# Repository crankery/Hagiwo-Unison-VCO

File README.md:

# Hagiwo Unison VCO

> [!NOTE]
> This is a work in progress, I'm sure I made a mistake somewhere I'll post an update when I receive the first batch of boards. 

If you don't know Hagiwo, check out their [YouTube channel](https://www.youtube.com/@HAGIWO). He puts out new DIY Eurorack module designs all the time.

This is (what is currently) has latest module, the [Unison VCO](https://note.com/solder_state/n/na0ae5754fa9c). All I've done is switch to SMT devices to try to fit it all on a single 6hp PCB. All credit for the circuit design go to Hagiwo.

The PCB is 100x30mm so it should be pretty darned cheap to order from one of the fabs over in China. Higawo used a [Seeed Studio XIAO RA4M1](https://wiki.seeedstudio.com/getting_started_xiao_ra4m1/) microcontroller module on this one, which are about $5 ordered from Seeed. They're really quite neat.

I added a tiny OLED display module to show the currently selected waveform. The display module is available from all the usual places with with search terms like "0.42" 0.42 Inch White OLED Display LCD Module 72X40 Serial Screen White Color I2C IIC/SPI Interface SSD1306". I'm sure there's an original manufacturer of these things but I can't figure it out. The 4 pin I2C SSD1306 version that looks like this:

TODO: make incredibly insightful comments about stuff here

## Main Board

Here's some renderings of this thing. I'll take pictures of it when I actually build it.

## Front Panel

I created a Eurorack 6hp front panel for this in KiCad. Which is weird but hey. I don't want to pay for aluminum panels.

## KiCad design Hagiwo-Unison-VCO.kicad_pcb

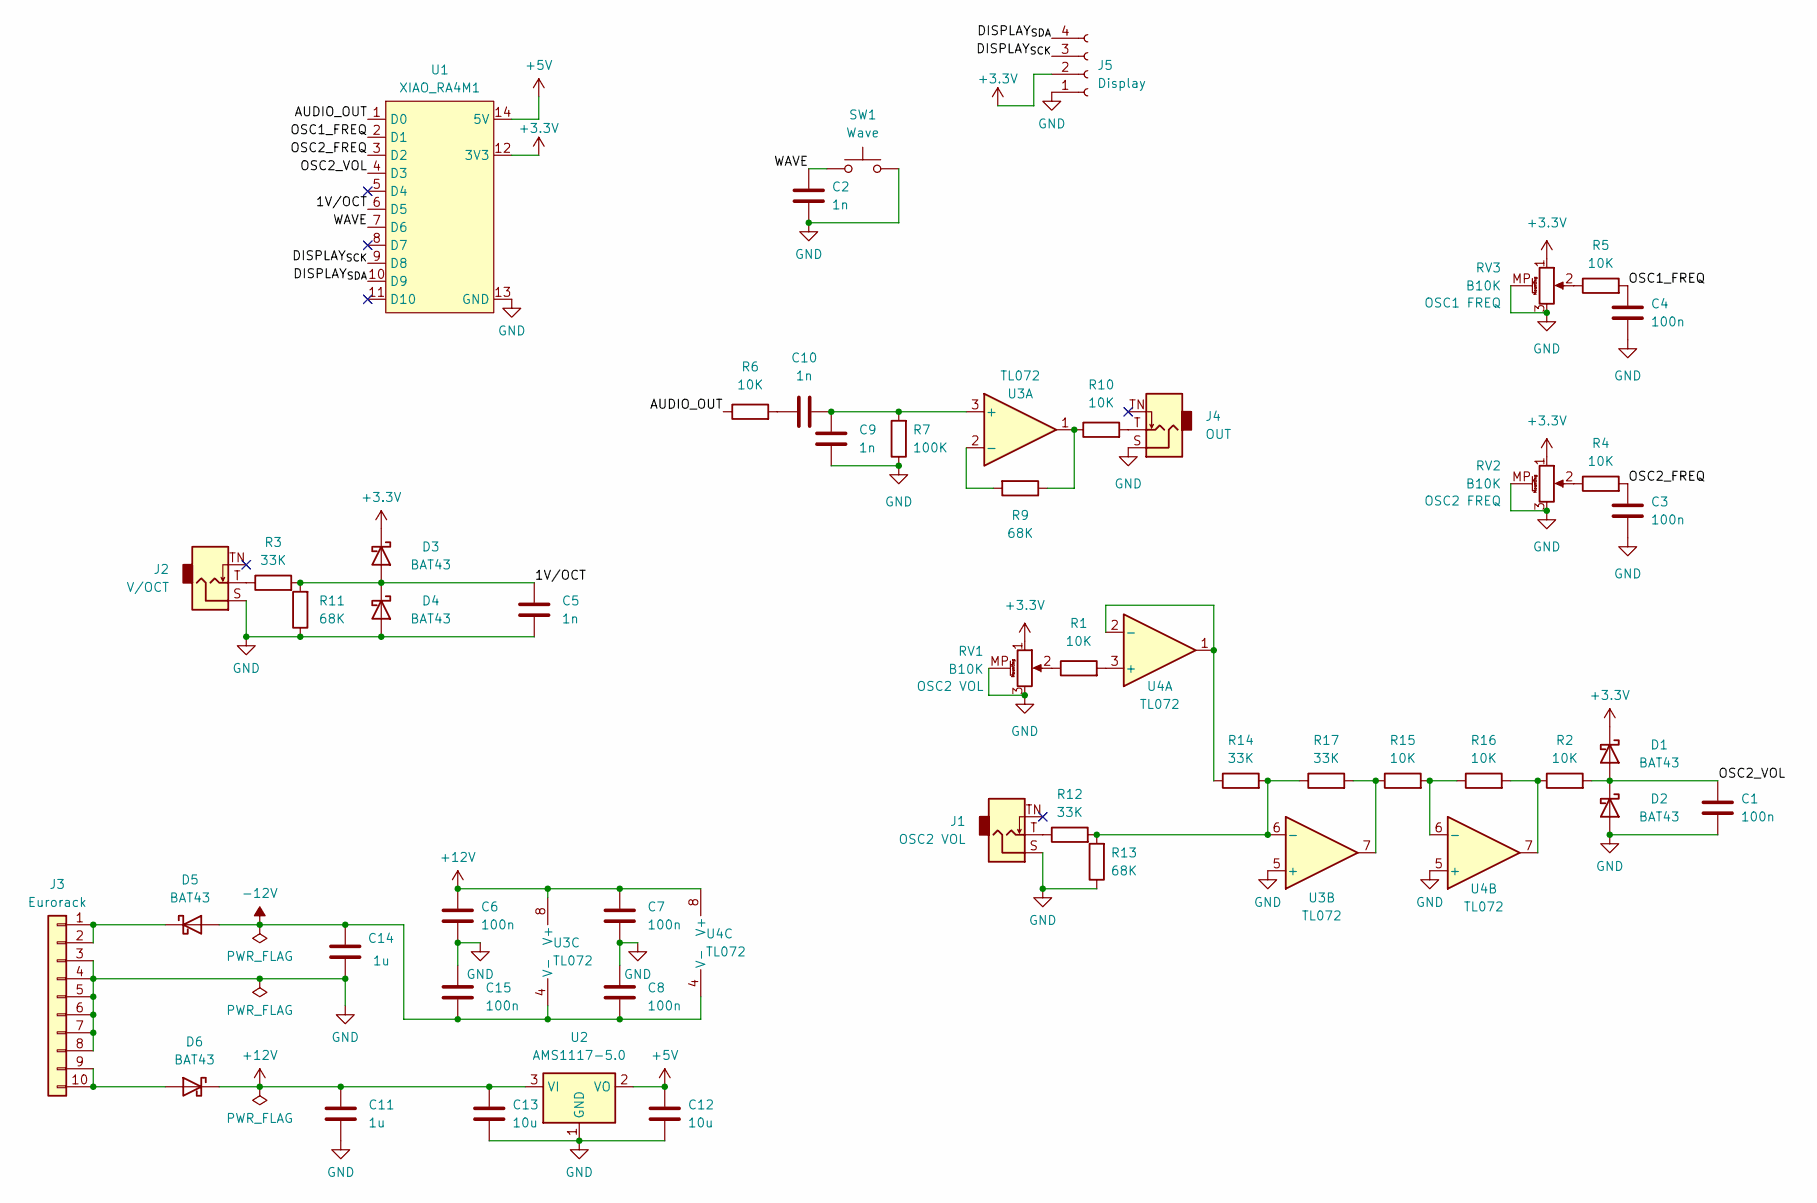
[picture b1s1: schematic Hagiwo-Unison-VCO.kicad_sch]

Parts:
C1, C3, C4, C6, C7, C8, C15: 100n; C_0805_2012Metric_Pad1.18x1.45mm_HandSolder
C2, C5, C9, C10: 1n; C_0805_2012Metric_Pad1.18x1.45mm_HandSolder
C11, C14: 1u; C_0805_2012Metric_Pad1.18x1.45mm_HandSolder
C12, C13: 10u; C_0805_2012Metric_Pad1.18x1.45mm_HandSolder
D1, D2, D3, D4, D5, D6: BAT43; D_SOD-123
J1: OSC2 VOL; Jack_3.5mm_QingPu_WQP-PJ398SM_Vertical_CircularHoles
J2: V/OCT; Jack_3.5mm_QingPu_WQP-PJ398SM_Vertical_CircularHoles
J3: Eurorack; PinHeader_2x05_P2.54mm_Vertical
J4: OUT; Jack_3.5mm_QingPu_WQP-PJ398SM_Vertical_CircularHoles
J5: Display; 0.42_OLED
R1, R2, R4, R5, R6, R10, R15, R16: 10K; R_0805_2012Metric_Pad1.20x1.40mm_HandSolder
R3, R12, R14, R17: 33K; R_0805_2012Metric_Pad1.20x1.40mm_HandSolder
R7: 100K; R_0805_2012Metric_Pad1.20x1.40mm_HandSolder
R9, R11, R13: 68K; R_0805_2012Metric_Pad1.20x1.40mm_HandSolder
RV1, RV2, RV3: B10K; Potentiometer_Alpha_RD901F-40-00D_Single_Vertical
SW1: Wave; SW_PUSH_6mm_H13mm
U1: XIAO_RA4M1; Seeed XIAO RA4M1 Basic
U2: AMS1117-5.0; SOT-223-3_TabPin2
U3, U4: TL072; SOIC-8_3.9x4.9mm_P1.27mm

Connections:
+3.3V: D1.1 (K), D3.1 (K), J5.2, RV1.1, RV2.1, RV3.1, U1.12 (3V3)
+5V: C12.2, U1.14 (5V), U2.2 (VO)
+12V: C6.2, C7.2, C11.2, C13.2, D6.1 (K), U2.3 (VI), U3.8 (V+), U4.8 (V+)
-12V: C8.1, C14.2, C15.1, D5.2 (A), U3.4 (V-), U4.4 (V-)
/1V/OCT: C5.2, D3.2 (A), D4.1 (K), R3.2, R11.2, U1.6 (D5)
/AUDIO_OUT: R6.1, U1.1 (D0)
/DISPLAY_{SCK}: J5.3, U1.9 (D8)
/DISPLAY_{SDA}: J5.4, U1.10 (D9)
/OSC1_FREQ: C4.2, R5.2, U1.2 (D1)
/OSC2_FREQ: C3.2, R4.2, U1.3 (D2)
/OSC2_VOL: C1.2, D1.2 (A), D2.1 (K), R2.2, U1.4 (D3)
/WAVE: C2.2, SW1.1, U1.7 (D6)
GND: C1.1, C2.1, C3.1, C4.1, C5.1, C6.1, C7.1, C8.2, C9.1, C11.1, C12.1, C13.1, C14.1, C15.2, D2.2 (A), D4.2 (A), J1.S, J2.S, J3.3, J3.4, J3.5, J3.6, J3.7, J3.8, J4.S, J5.1, R7.1, R11.1, R13.1, RV1.3, RV1.MP (MountPin), RV2.3, RV2.MP (MountPin), RV3.3, RV3.MP (MountPin), SW1.2, U1.13 (GND), U2.1 (GND), U3.5 (+), U4.5 (+)
unnamed: C10.2, R6.2
unnamed: D5.1 (K), J3.1, J3.2
unnamed: D6.2 (A), J3.9, J3.10
unnamed: J1.T, R12.1
unnamed: J2.T, R3.1
unnamed: J4.T, R10.2
unnamed: R1.1, RV1.2
unnamed: R4.1, RV2.2
unnamed: R5.1, RV3.2
unnamed: R9.1, R10.1, U3.1
unnamed: R15.1, R17.2, U3.7
unnamed: R2.1, R16.2, U4.7
unnamed: C9.2, C10.1, R7.2, U3.3 (+)
unnamed: R9.2, U3.2 (-)
unnamed: R12.2, R13.2, R14.2, R17.1, U3.6 (-)
unnamed: R1.2, U4.3 (+)
unnamed: R14.1, U4.1, U4.2 (-)
unnamed: R15.2, R16.1, U4.6 (-)

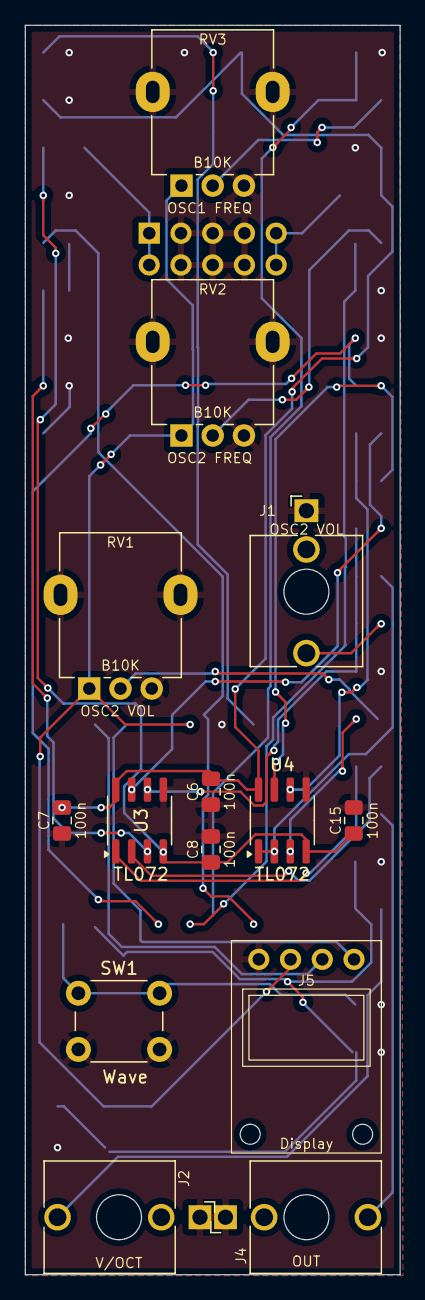
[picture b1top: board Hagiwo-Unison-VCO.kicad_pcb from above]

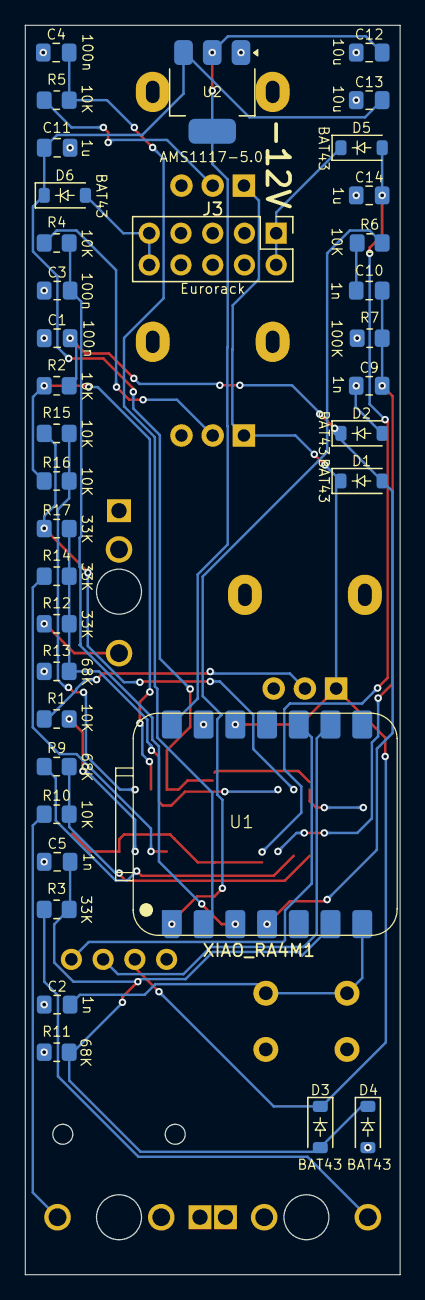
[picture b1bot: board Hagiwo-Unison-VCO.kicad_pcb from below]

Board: 2 copper layers, 30.0 x 100.0 mm, 50 parts (36 on the bottom side), 31 nets.

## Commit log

2024-11-03 clean up
2024-11-04 add a pcb front panel
2024-11-04 why not make a front panel? lol
2024-11-04 add some photos for the readme.
